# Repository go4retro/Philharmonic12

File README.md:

# Philharmonic 12 

A 12 Voice Hardware Music Synthesizer for the TANDY Color Computer and Dragon

This cartridge reproduces the functionality of the Speech Systems "Symphony 12" cartridge.

NOTE:  As of 2018-12-24, this design has not been built and tested.  Caveat Emptor!

## Reproduction Changes
Although the schematic on page 27 of the Owner's Manual was followed to implement this reproduction, the schematic was incomplete, and so a few changes were made to minimize parts count and fill in the gaps.

The decoding of the MC6821 /CS2 line was defined as "pin 15 74ls138 $ff60", which implied that $ff60 would represent a low level on pin 15 of the IC (a 3-8 decoder), which is value "0".  That meant input lines A,B, and C must be low levels.  Since address lines 0 and 1 select the specific MC6821 register, it is assumed address lines 2,3, and 4 are sent to inputs A, B, and C.  Furthermore, since the unit decodes to $ff60, which is above the /SCS space, a full address decode must be done.  A 74LS30 8 input NAND gate was used to decode an $ffxx access, and that output was used to gate the '138.  Address lines 7, 6, and 5 were still not decoded, but must be set to 011.  Thus, A7 was sent to a negative select line on the '138, while A5 and A6 were sent to active high select lines on the MC6821 (which are tied to +5V on the original schematic).  THis change should not affect functionality.

Another difference lies in the clock signal for the sound ICs.  The original schematic ties the sound clock to 6809 E clock, which provides a stable .895MHz signal on all computers except for the Color Computer 3.  On the CoCo 3, the E clock can be set to .895MHz or 1.79MHz.  This will affect the pitch of the audio considerably.  Thus, a stable .895MHz oscillator was included on the PCB design, though a jumper cna still be used to select the E clock if desired.

Finally, the AY-3-8912 ICs used in the original design are harder to find than the larger cousin, the AY-3-8910.  Thus, this design used the larger and cheaper ICs.

## License
Copyright (C) 2018  RETRO Innovations

These files are free designs; you can redistribute them and/or modify
them under the terms of the Creative Commons Attribution-ShareAlike 
4.0 International License.

You should have received a copy of the license along with this
work. If not, see <http://creativecommons.org/licenses/by-sa/4.0/>.

These files are distributed in the hope that they will be useful,
but WITHOUT ANY WARRANTY; without even the implied warranty of
MERCHANTABILITY or FITNESS FOR A PARTICULAR PURPOSE.  See the
license for more details.

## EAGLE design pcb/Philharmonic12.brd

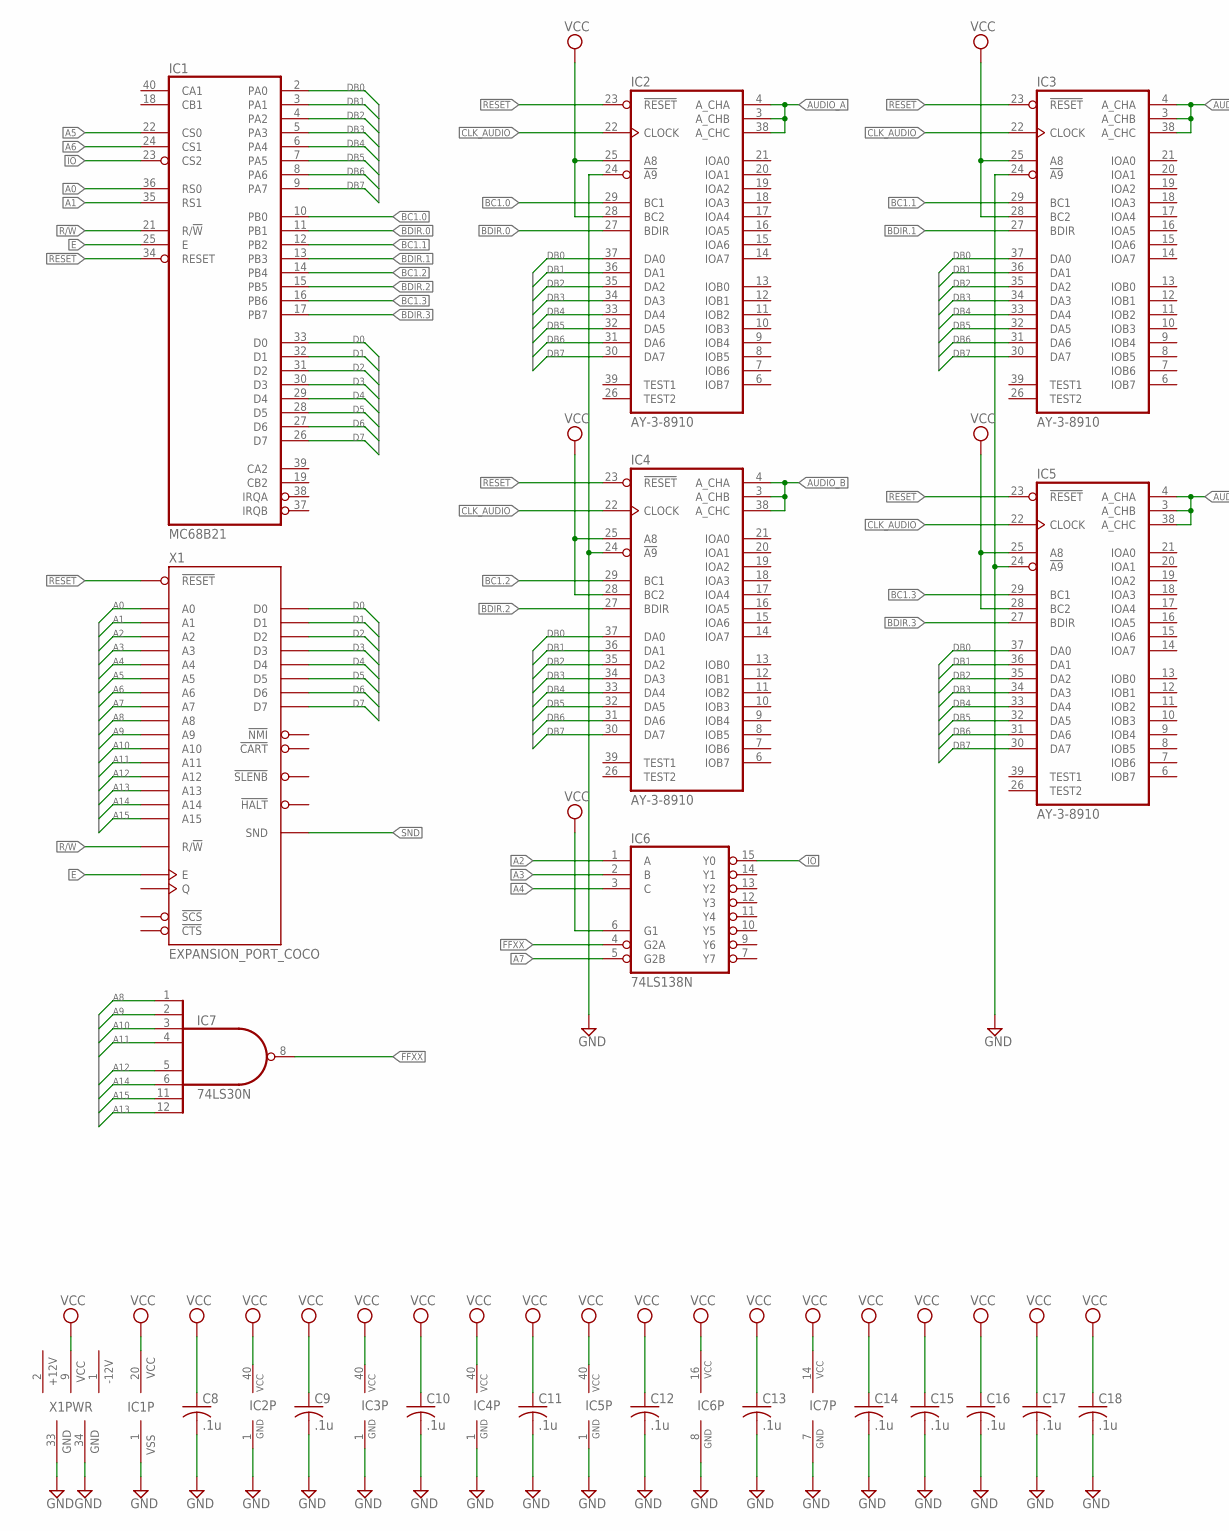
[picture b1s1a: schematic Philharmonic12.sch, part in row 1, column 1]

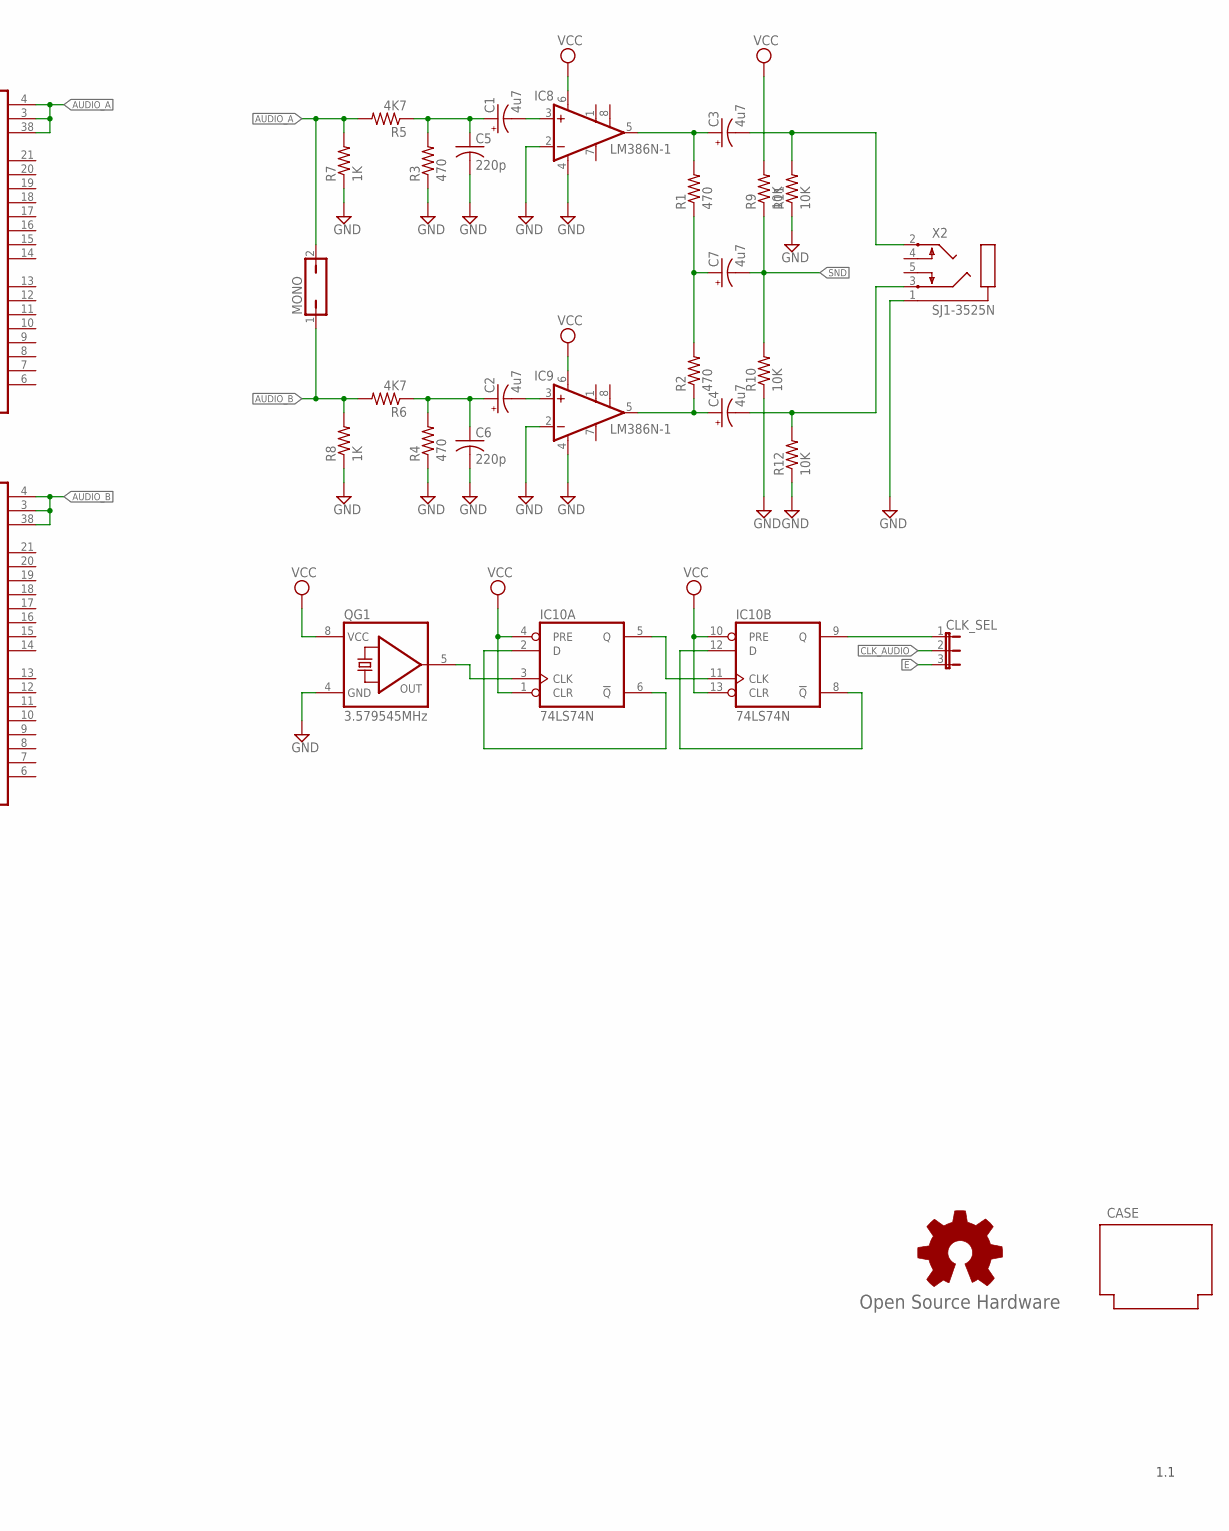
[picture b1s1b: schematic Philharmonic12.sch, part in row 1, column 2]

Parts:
C1, C2, C3, C4, C7: 4u7; E2,5-6
C5, C6: 220p; C025-025X050
C8, C9, C10, C11, C12, C13, C14, C15, C16, C17, C18: .1u; C025-025X050
CASE: PROGRAM_PAK
CLK_SEL: JP2E; JP2
GOLD_ORB_SM1: Open Source Hardware; OSHW_5MM
IC1: MC68B21; DIL40-ROUNDPAD
IC2, IC3, IC4, IC5: AY-3-8910; DIL40-RP
IC6: 74LS138N; DIL16-RP
IC7: 74LS30N; DIL14-RP
IC8, IC9: LM386N-1; DIL08
IC10: 74LS74N; DIL14-RP
MONO: JP1Q; JP1
QG1: 3.579545MHz; DIL08S
R1, R2, R3, R4: 470; 0204/7
R5, R6: 4K7; 0204/7
R7, R8: 1K; 0204/7
R9, R10, R11, R12: 10K; 0204/7
X1: EXPANSION_PORT_COCO; MA20-2
X2: SJ1-3525N

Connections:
!FFXX: IC6.4 (G2A), IC7.8 (O)
!IO: IC1.23 (CS2), IC6.15 (Y0)
!RESET: IC1.34 (RESET), IC2.23 (!RESET), IC3.23 (!RESET), IC4.23 (!RESET), IC5.23 (!RESET), X1.5 (!RESET)
+12V: X1.2 (+12V)
-12V: X1.1 (-12V)
A0: IC1.36 (RS0), X1.19 (A0)
A1: IC1.35 (RS1), X1.20 (A1)
A2: IC6.1 (A), X1.21 (A2)
A3: IC6.2 (B), X1.22 (A3)
A4: IC6.3 (C), X1.23 (A4)
A5: IC1.22 (CS0), X1.24 (A5)
A6: IC1.24 (CS1), X1.25 (A6)
A7: IC6.5 (G2B), X1.26 (A7)
A8: IC7.1 (I0), X1.27 (A8)
A9: IC7.2 (I1), X1.28 (A9)
A10: IC7.3 (I2), X1.29 (A10)
A11: IC7.4 (I3), X1.30 (A11)
A12: IC7.5 (I4), X1.31 (A12)
A13: IC7.12 (I7), X1.37 (A13)
A14: IC7.6 (I5), X1.38 (A14)
A15: IC7.11 (I6), X1.39 (A15)
AUDIO_A: IC2.3 (A_CHB), IC2.4 (A_CHA), IC2.38 (A_CHC), IC3.3 (A_CHB), IC3.4 (A_CHA), IC3.38 (A_CHC), MONO.2, R5.2, R7.2
AUDIO_B: IC4.3 (A_CHB), IC4.4 (A_CHA), IC4.38 (A_CHC), IC5.3 (A_CHB), IC5.4 (A_CHA), IC5.38 (A_CHC), MONO.1, R6.2, R8.2
BC1.0: IC1.10 (PB0), IC2.29 (BC1)
BC1.1: IC1.12 (PB2), IC3.29 (BC1)
BC1.2: IC1.14 (PB4), IC4.29 (BC1)
BC1.3: IC1.16 (PB6), IC5.29 (BC1)
BDIR.0: IC1.11 (PB1), IC2.27 (BDIR)
BDIR.1: IC1.13 (PB3), IC3.27 (BDIR)
BDIR.2: IC1.15 (PB5), IC4.27 (BDIR)
BDIR.3: IC1.17 (PB7), IC5.27 (BDIR)
CLK: IC10.3 (CLK), QG1.5 (OUT)
CLK/2: IC10.5 (Q), IC10.11 (CLK)
CLK/4: CLK_SEL.1, IC10.9 (Q)
CLK_AUDIO: CLK_SEL.2, IC2.22 (CLOCK), IC3.22 (CLOCK), IC4.22 (CLOCK), IC5.22 (CLOCK)
D0: IC1.33 (D0), X1.10 (D0)
D1: IC1.32 (D1), X1.11 (D1)
D2: IC1.31 (D2), X1.12 (D2)
D3: IC1.30 (D3), X1.13 (D3)
D4: IC1.29 (D4), X1.14 (D4)
D5: IC1.28 (D5), X1.15 (D5)
D6: IC1.27 (D6), X1.16 (D6)
D7: IC1.26 (D7), X1.17 (D7)
DB0: IC1.2 (PA0), IC2.37 (DA0), IC3.37 (DA0), IC4.37 (DA0), IC5.37 (DA0)
DB1: IC1.3 (PA1), IC2.36 (DA1), IC3.36 (DA1), IC4.36 (DA1), IC5.36 (DA1)
DB2: IC1.4 (PA2), IC2.35 (DA2), IC3.35 (DA2), IC4.35 (DA2), IC5.35 (DA2)
DB3: IC1.5 (PA3), IC2.34 (DA3), IC3.34 (DA3), IC4.34 (DA3), IC5.34 (DA3)
DB4: IC1.6 (PA4), IC2.33 (DA4), IC3.33 (DA4), IC4.33 (DA4), IC5.33 (DA4)
DB5: IC1.7 (PA5), IC2.32 (DA5), IC3.32 (DA5), IC4.32 (DA5), IC5.32 (DA5)
DB6: IC1.8 (PA6), IC2.31 (DA6), IC3.31 (DA6), IC4.31 (DA6), IC5.31 (DA6)
DB7: IC1.9 (PA7), IC2.30 (DA7), IC3.30 (DA7), IC4.30 (DA7), IC5.30 (DA7)
E: CLK_SEL.3, IC1.25 (E), X1.6 (E)
GND: C5.2, C6.2, C8.2, C9.2, C10.2, C11.2, C12.2, C13.2, C14.2, C15.2, C16.2, C17.2, C18.2, IC1.1 (VSS), IC2.1 (GND), IC2.24 (!A9), IC3.1 (GND), IC3.24 (!A9), IC4.1 (GND), IC4.24 (!A9), IC5.1 (GND), IC5.24 (!A9), IC6.8 (GND), IC7.7 (GND), IC8.2 (-IN), IC8.4 (GND), IC9.2 (-IN), IC9.4 (GND), IC10.7 (GND), QG1.4 (GND), R3.1, R4.1, R7.1, R8.1, R10.1, R11.1, R12.1, X1.33 (GND), X1.34 (GND), X2.1
unnamed: IC10.2 (D), IC10.6 (!Q)
unnamed: C7.+, R1.1, R2.2
unnamed: C4.-, R12.2, X2.3
unnamed: C3.+, IC8.5 (OUT), R1.2
unnamed: C4.+, IC9.5 (OUT), R2.1
unnamed: C1.-, IC8.3 (+IN)
unnamed: C1.+, C5.1, R3.2, R5.1
unnamed: C2.-, IC9.3 (+IN)
unnamed: C2.+, C6.1, R4.2, R6.1
unnamed: IC10.8 (!Q), IC10.12 (D)
unnamed: C3.-, R11.2, X2.2
R/!W: IC1.21 (R/!W), X1.18 (R/!W)
SND: C7.-, R9.1, R10.2, X1.35 (SND)
VCC: C8.1, C9.1, C10.1, C11.1, C12.1, C13.1, C14.1, C15.1, C16.1, C17.1, C18.1, IC1.20 (VCC), IC2.25 (A8), IC2.28 (BC2), IC2.40 (VCC), IC3.25 (A8), IC3.28 (BC2), IC3.40 (VCC), IC4.25 (A8), IC4.28 (BC2), IC4.40 (VCC), IC5.25 (A8), IC5.28 (BC2), IC5.40 (VCC), IC6.6 (G1), IC6.16 (VCC), IC7.14 (VCC), IC8.6 (VS), IC9.6 (VS), IC10.1 (CLR), IC10.4 (PRE), IC10.10 (PRE), IC10.13 (CLR), IC10.14 (VCC), QG1.8 (VCC), R9.2, X1.9 (VCC)

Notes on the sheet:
1.1

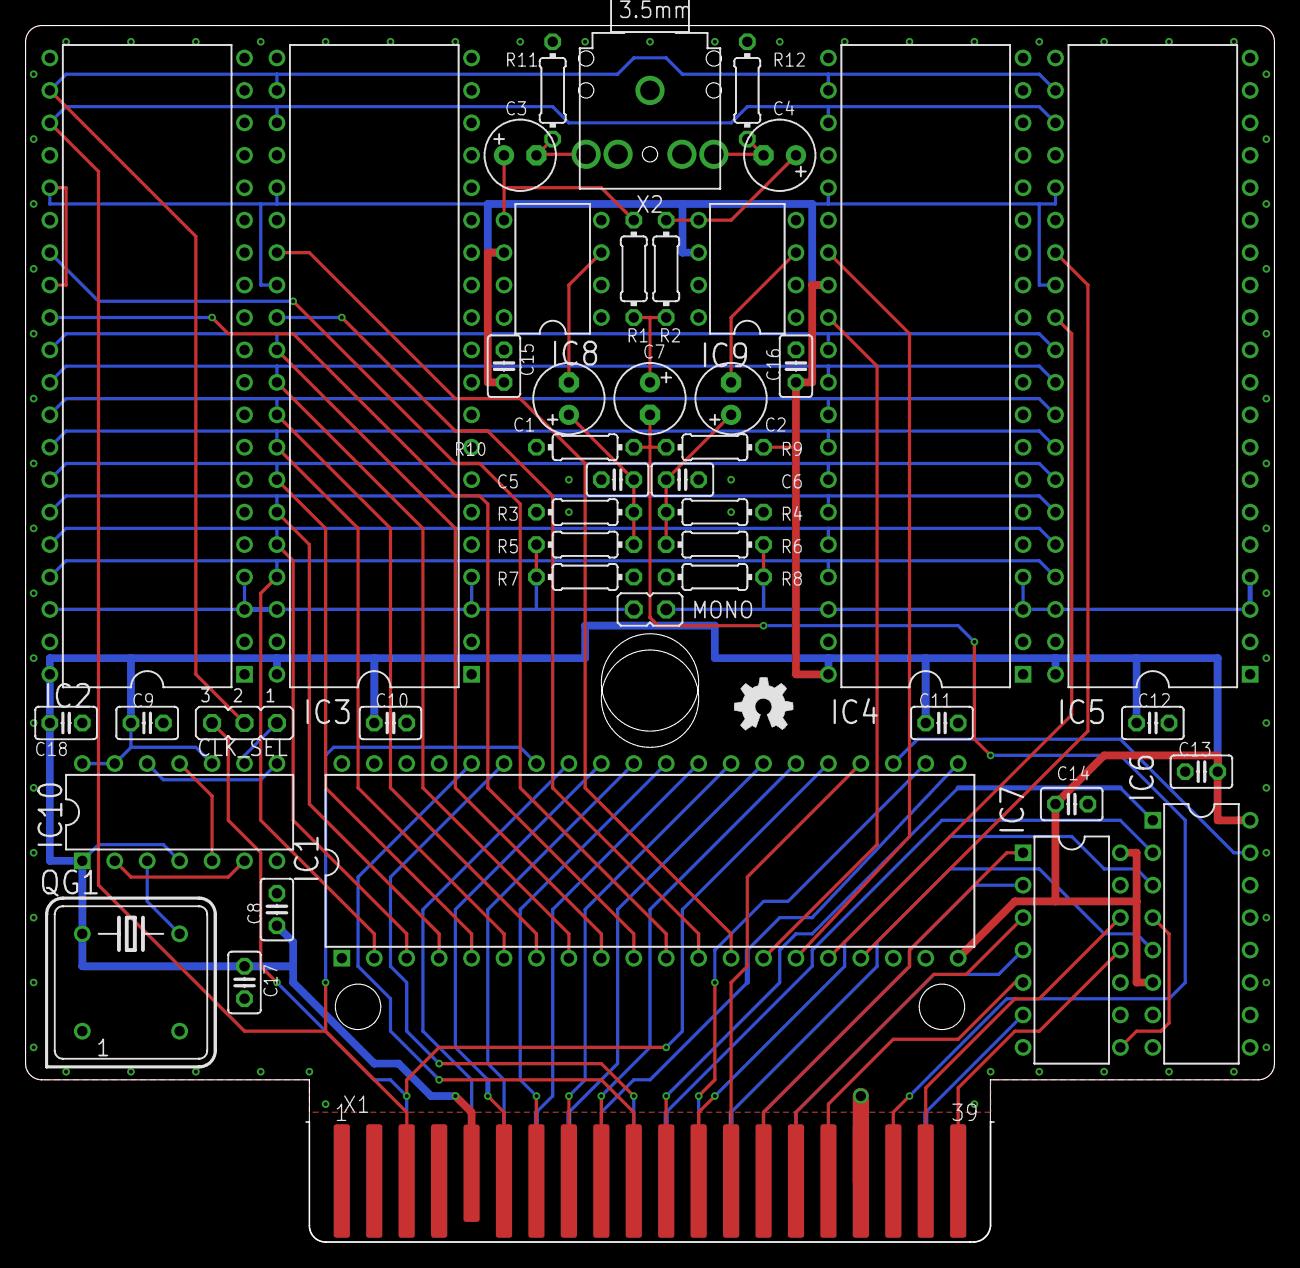
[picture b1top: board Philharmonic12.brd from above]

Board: 2 copper layers, 97.8 x 95.2 mm, 47 parts (0 on the bottom side), 65 nets.

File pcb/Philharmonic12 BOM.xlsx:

Part | Quantity | Value | Description | Note: | Link
C1,C2,C3,C4,C7 | 5 | 4u7 | POLARIZED CAPACITOR, American symbol | 10V or better is fine | https://www.digikey.com/en/products/detail/w-rth-elektronik/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
C5,C6 | 2 | 220p | CAPACITOR, American symbol | 10V or better is fine | https://www.digikey.com/en/products/detail/vishay-beyschlag-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
C8,9,10,11,12,13,14,15,16,17,18 | 11 | .1u | CAPACITOR, American symbol | 10V or better is fine | https://www.digikey.com/en/products/detail/vishay-beyschlag-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
CLK_SEL, MONO | 1 |  | JUMPER | break into 1 1x2 and 1 1x3 | https://www.digikey.com/en/products/detail/amphenol-icc-fci/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
IC1 | 1 | MC68B21 | MICROCONTROLLER/MEMORY DEVICE | Must be 'B' speed grade if used on CoCo 3 | https://www.utsource.net/itm/p/135503.html
IC2,3,4,5 | 4 | AY-3-8910 | Programmable sound generator | YM-2149 can be used as well | https://www.utsource.net/itm/p/446115.html
IC6 | 1 | 74LS138N | 3-line to 8-line DECODER/DEMULTIPLEXER | must be at least as fast as LS | https://www.digikey.com/en/products/detail/texas-instruments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
IC7 | 1 | 74LS30N | 8-input NAND gate | must be at least as fast as LS | https://www.digikey.com/en/products/detail/texas-instruments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
IC8,9 | 2 | LM386N-1 | Low Voltage Audio Power Amplifier |  | https://www.digikey.com/en/products/detail/texas-instruments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
IC10 | 1 | 74LS74N | Dual D type positive edge triggered FLIP FLOP, preset and clear | hct and other families will work | https://www.digikey.com/en/products/detail/texas-instruments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
 | 2 |  | Shorting Blocks | nothing special | https://www.digikey.com/en/products/detail/kycon-inc/SX1100-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
QG1 | 1 | 3.579545MHz | CRYSTAL RESONATOR |  | https://www.digikey.com/en/products/detail/ecs-inc/ECS-2100A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
R1,2,3,4 | 4 | 470 | RESISTOR, American symbol | Any 1/8W | https://www.digikey.com/en/products/detail/stackpole-electro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
R5,6 | 2 | 4K7 | RESISTOR, American symbol | Any 1/8W | https://www.digikey.com/en/products/detail/stackpole-electro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
R7,8 | 2 | 1K | RESISTOR, American symbol | Any 1/8W | https://www.digikey.com/en/products/detail/stackpole-electro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
R9,10,11,12 | 4 | 10K | RESISTOR, American symbol | Any 1/8W | https://www.digikey.com/en/products/detail/stackpole-electro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
X2 | 1 | SJ1-3523N | 3.5mm Stereo Jack | can also use SJ1-3524 or 3525 | https://www.digikey.com/en/products/detail/cui-devices/SJ1-3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

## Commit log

2018-12-25 Ensure folks know the design has not been tested
2018-12-25 Fixed typos
2018-12-25 Can't get .895MHz oscillators, so modified to use 3.59MHz and /4 divider.
2019-02-03 Added parts values
2019-10-28 Minor silkscreen updates
2020-01-11 CoCo Cart Port was slightly too narrow. Widened to make for snug fit.
2020-04-23 Small dimension updates
2020-10-13 Updates to schematic, Added BOM, and added sample code written by Chet Simpson
2020-10-13 Added populated PCB picture
2023-09-04 Fix PCB legend placement error noted in Issue #1 (hexbus reported)
2025-08-09 Add pics

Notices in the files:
pcb/Philharmonic12.brd:
PCB (c) 2018 RETRO Innovations
CC-BY-SA 4.0
